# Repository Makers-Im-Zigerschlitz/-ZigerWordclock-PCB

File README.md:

# ZigerWordclock-PCB
KiCad PCB data for our OpenSource Wordclock

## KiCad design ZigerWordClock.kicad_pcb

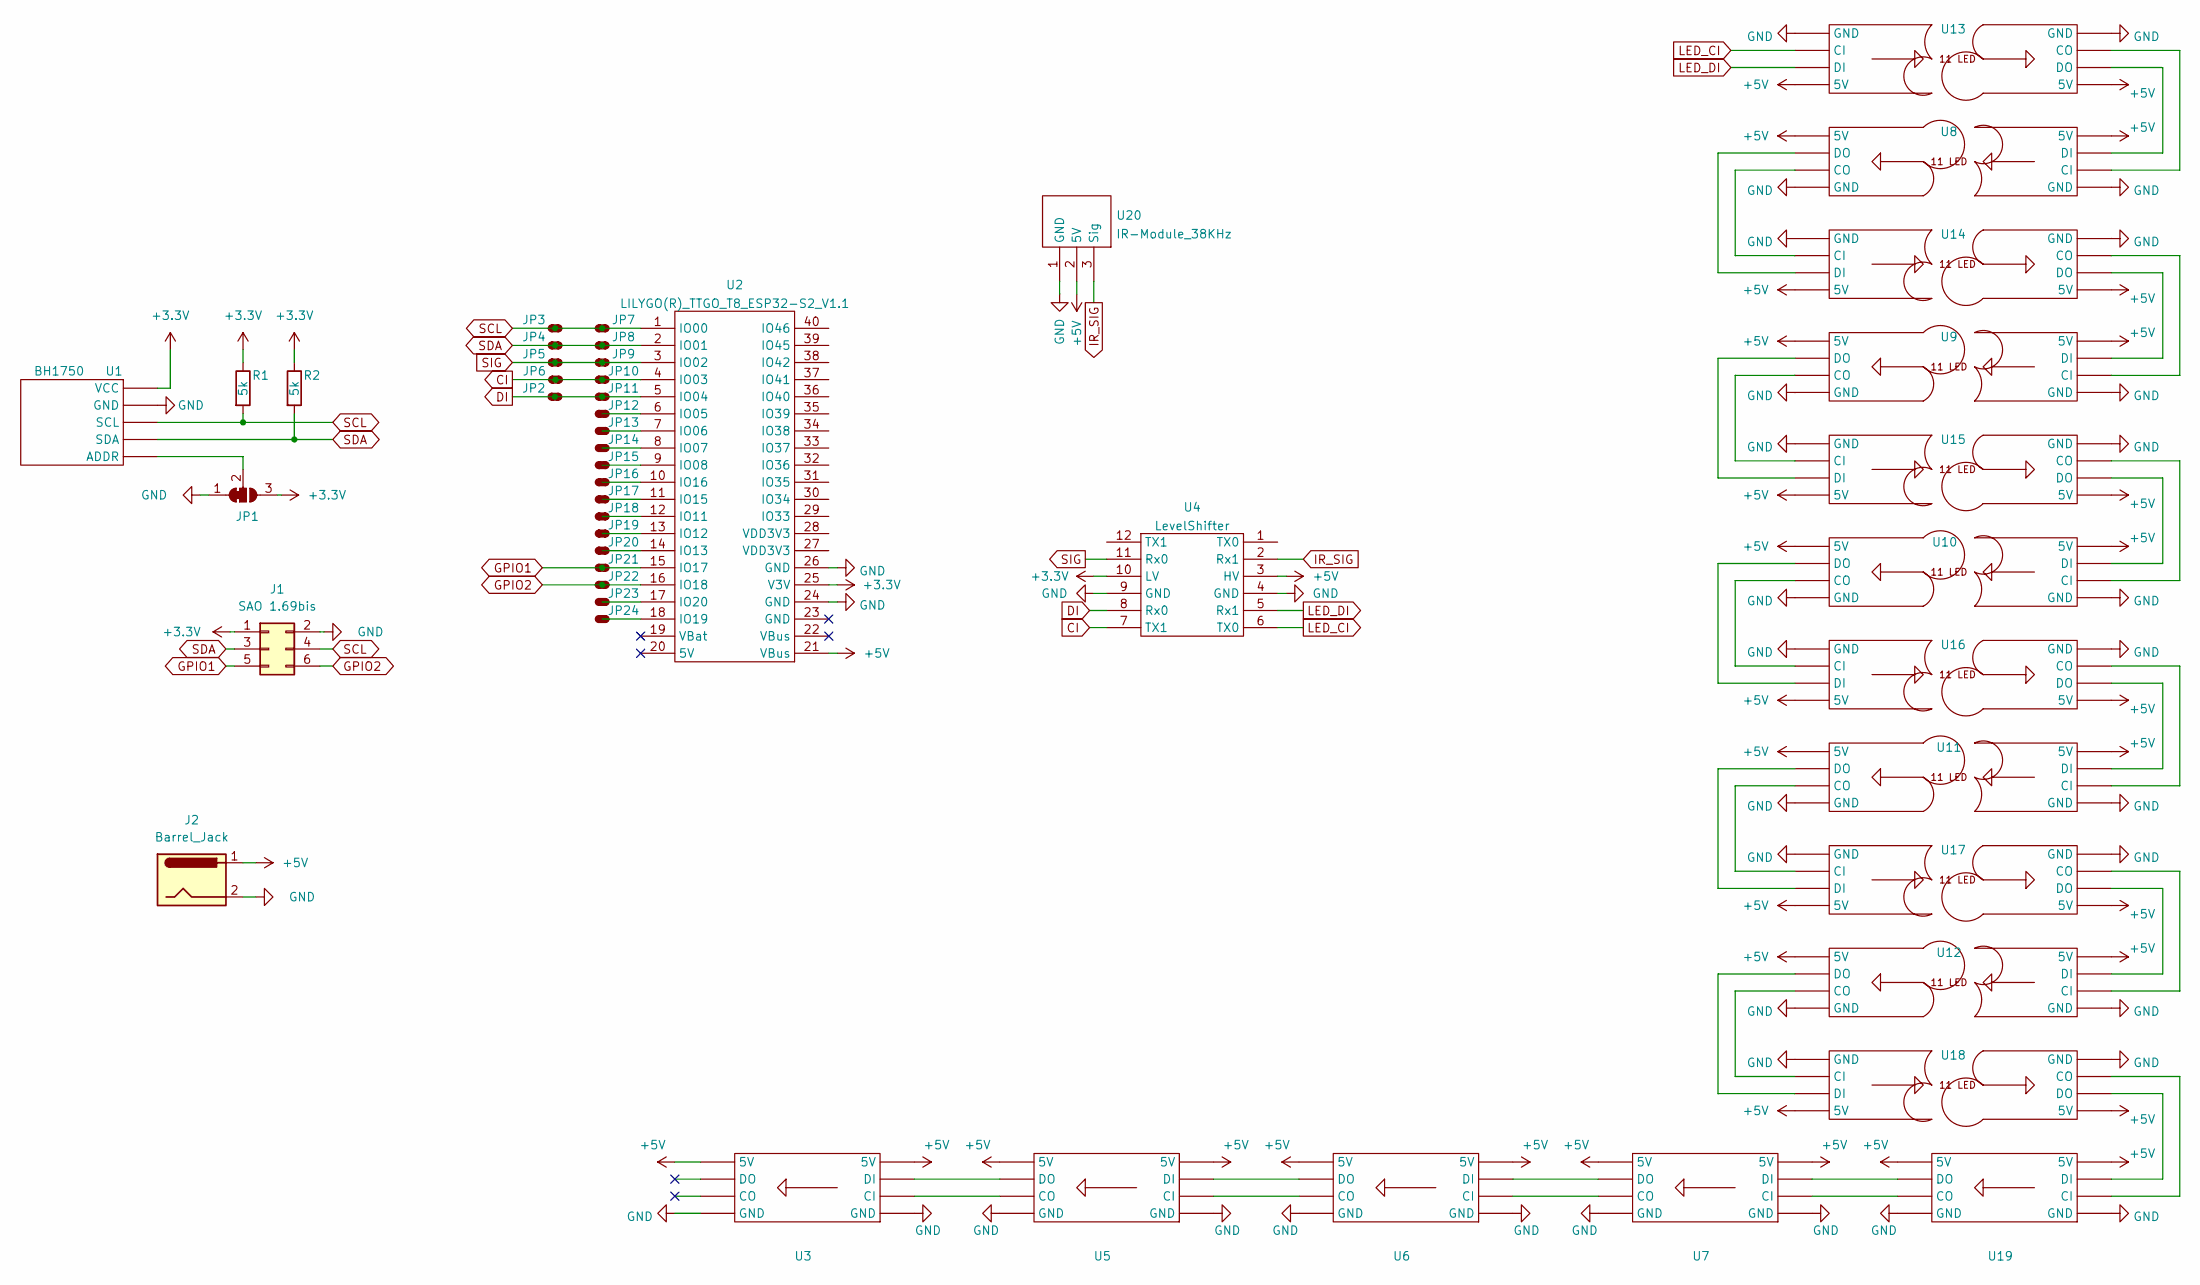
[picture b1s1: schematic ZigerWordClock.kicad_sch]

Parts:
J1: SAO 1.69bis; PinSocket_2x03_P2.54mm_Vertical_SMD
J2: Barrel_Jack; PinHeader_1x02_P2.54mm_Vertical
JP1: SolderJumper_3_Bridged12; SolderJumper-3_P1.3mm_Bridged12_RoundedPad1.0x1.5mm_NumberL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
JP2, JP3, JP4, JP5, JP6, JP7, JP8, JP9, JP10, JP11, JP12, JP13, JP14, JP15, JP16, JP17, JP18, JP19, JP20, JP21, JP22, JP23, JP24: Pad
R1, R2: 5k; R_Axial_DIN0207_L6.3mm_D2.5mm_P10.16mm_Horizontal
U1: BH1750; BH1750 Breakout Board
U2: LILYGO(R)_TTGO_T8_ESP32-S2_V1.1; LILYGO® TTGO T8 ESP32-S2 V1.1
U3, U5, U6, U7, U19: BTF-5V-060L-B_SK9822_LED_Strip_-_1_LED; BTF-5V-060L-B SK9822 LED Strip - 1 Segment
U4: LevelShifter
U8, U9, U10, U11, U12, U13, U14, U15, U16, U17, U18: BTF-5V-060L-B_SK9822_LED_Strip_-_11_LED; BTF-5V-060L-B SK9822 LED Strip - 11 Segment
U20: IR-Module_38KHz

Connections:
+3V3: J1.1, JP1.3 (B), R1.1, R2.1, U1.VCC, U2.25 (V3V), U4.10 (LV)
+5V: J2.1, U2.21 (VBus), U3.5V_1 (5V), U3.5V_2 (5V), U4.3 (HV), U5.5V_1 (5V), U5.5V_2 (5V), U6.5V_1 (5V), U6.5V_2 (5V), U7.5V_1 (5V), U7.5V_2 (5V), U8.5V_1 (5V), U8.5V_2 (5V), U9.5V_1 (5V), U9.5V_2 (5V), U10.5V_1 (5V), U10.5V_2 (5V), U11.5V_1 (5V), U11.5V_2 (5V), U12.5V_1 (5V), U12.5V_2 (5V), U13.5V_1 (5V), U13.5V_2 (5V), U14.5V_1 (5V), U14.5V_2 (5V), U15.5V_1 (5V), U15.5V_2 (5V), U16.5V_1 (5V), U16.5V_2 (5V), U17.5V_1 (5V), U17.5V_2 (5V), U18.5V_1 (5V), U18.5V_2 (5V), U19.5V_1 (5V), U19.5V_2 (5V), U20.2 (5V)
CI: JP6.1, JP10.1, U2.4 (IO03), U4.7 (TX1)
DI: JP2.1, JP11.1, U2.5 (IO04), U4.8 (Rx0)
GND: J1.2, J2.2, JP1.1 (A), U1.GND, U2.24 (GND), U2.26 (GND), U3.GND_1 (GND), U3.GND_2 (GND), U4.4 (GND), U4.9 (GND), U5.GND_1 (GND), U5.GND_2 (GND), U6.GND_1 (GND), U6.GND_2 (GND), U7.GND_1 (GND), U7.GND_2 (GND), U8.GND_1 (GND), U8.GND_2 (GND), U9.GND_1 (GND), U9.GND_2 (GND), U10.GND_1 (GND), U10.GND_2 (GND), U11.GND_1 (GND), U11.GND_2 (GND), U12.GND_1 (GND), U12.GND_2 (GND), U13.GND_1 (GND), U13.GND_2 (GND), U14.GND_1 (GND), U14.GND_2 (GND), U15.GND_1 (GND), U15.GND_2 (GND), U16.GND_1 (GND), U16.GND_2 (GND), U17.GND_1 (GND), U17.GND_2 (GND), U18.GND_1 (GND), U18.GND_2 (GND), U19.GND_1 (GND), U19.GND_2 (GND), U20.1 (GND)
GPIO1: J1.5, JP21.1, U2.15 (IO17)
GPIO2: J1.6, JP22.1, U2.16 (IO18)
IR_SIG: U4.2 (Rx1), U20.3 (Sig)
LED_CI: U4.6 (TX0), U13.CI
LED_DI: U4.5 (Rx1), U13.DI
unnamed: JP1.2 (C), U1.ADDR
unnamed: JP12.1, U2.6 (IO05)
unnamed: JP13.1, U2.7 (IO06)
unnamed: JP14.1, U2.8 (IO07)
unnamed: JP15.1, U2.9 (IO08)
unnamed: JP16.1, U2.10 (IO16)
unnamed: JP17.1, U2.11 (IO15)
unnamed: JP18.1, U2.12 (IO11)
unnamed: JP19.1, U2.13 (IO12)
unnamed: JP20.1, U2.14 (IO13)
unnamed: JP23.1, U2.17 (IO20)
unnamed: JP24.1, U2.18 (IO19)
unnamed: U3.CI, U5.CO
unnamed: U3.DI, U5.DO
unnamed: U5.CI, U6.CO
unnamed: U5.DI, U6.DO
unnamed: U6.CI, U7.CO
unnamed: U6.DI, U7.DO
unnamed: U10.CI, U15.CO
unnamed: U10.CO, U16.CI
unnamed: U10.DI, U15.DO
unnamed: U10.DO, U16.DI
unnamed: U11.CI, U16.CO
unnamed: U11.CO, U17.CI
unnamed: U11.DI, U16.DO
unnamed: U11.DO, U17.DI
unnamed: U12.CI, U17.CO
unnamed: U12.CO, U18.CI
unnamed: U12.DI, U17.DO
unnamed: U12.DO, U18.DI
unnamed: U8.CI, U13.CO
unnamed: U8.DI, U13.DO
unnamed: U8.CO, U14.CI
unnamed: U9.CI, U14.CO
unnamed: U8.DO, U14.DI
unnamed: U9.DI, U14.DO
unnamed: U9.CO, U15.CI
unnamed: U9.DO, U15.DI
unnamed: U18.CO, U19.CI
unnamed: U18.DO, U19.DI
unnamed: U7.CI, U19.CO
unnamed: U7.DI, U19.DO
SCL: J1.4, JP3.1, JP7.1, R1.2, U1.SCL, U2.1 (IO00)
SDA: J1.3, JP4.1, JP8.1, R2.2, U1.SDA, U2.2 (IO01)
SIG: JP5.1, JP9.1, U2.3 (IO02), U4.11 (Rx0)

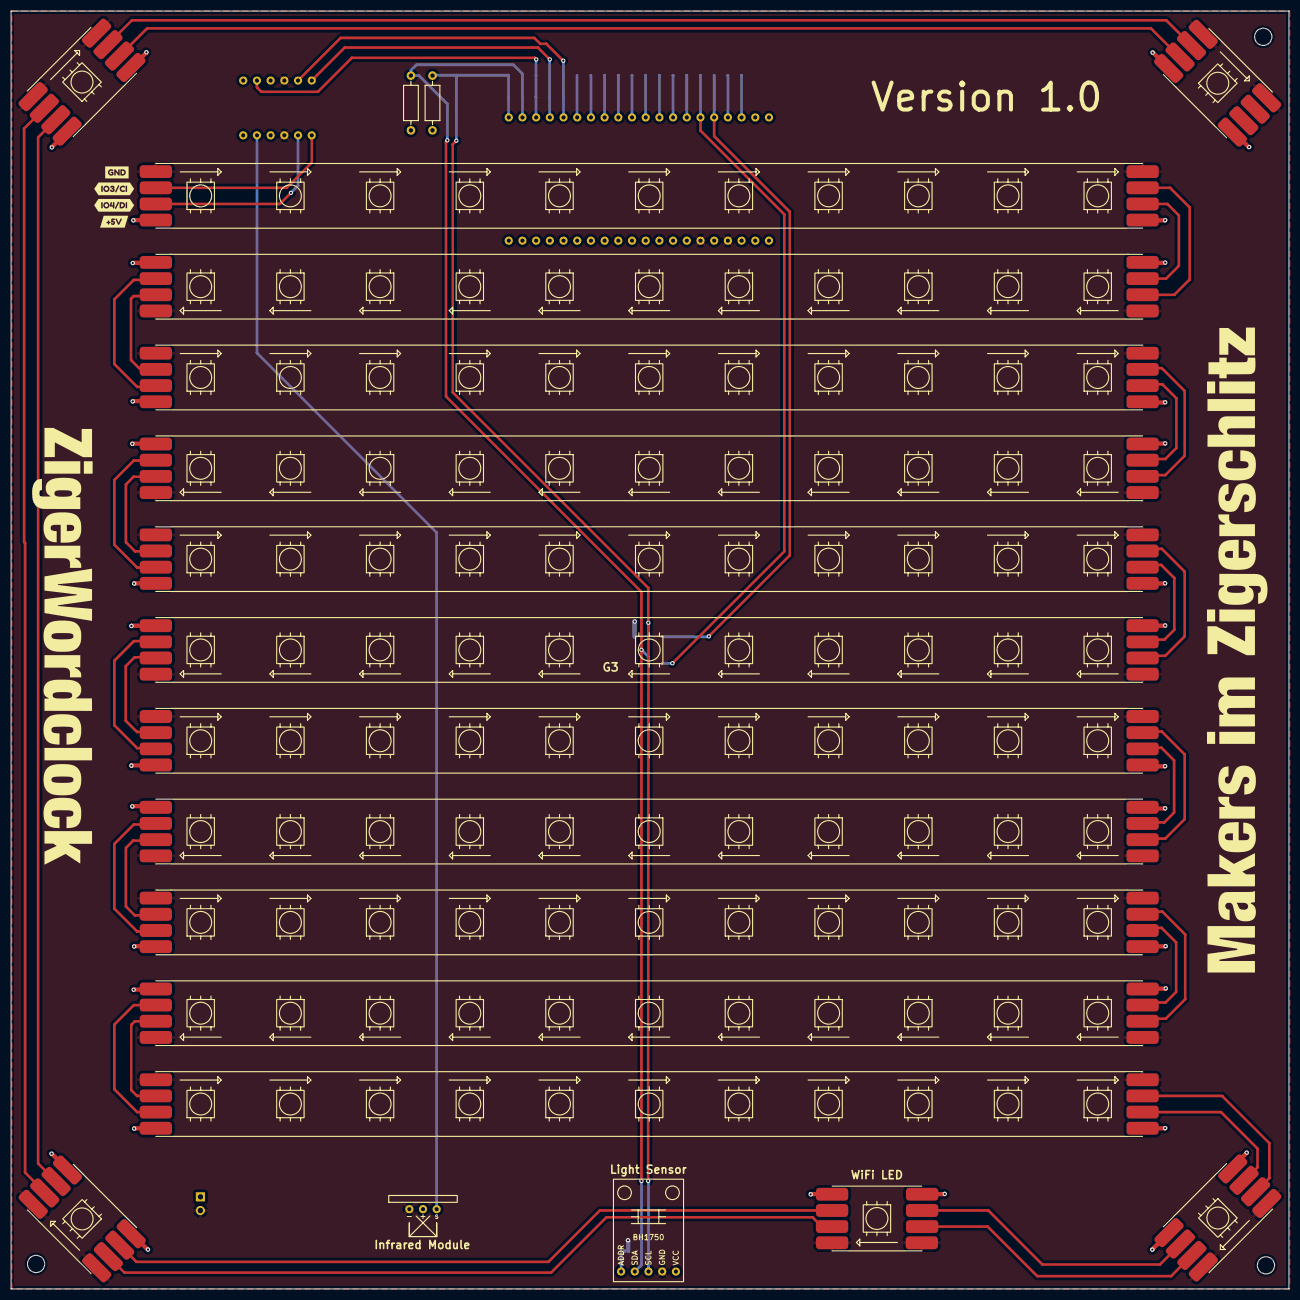
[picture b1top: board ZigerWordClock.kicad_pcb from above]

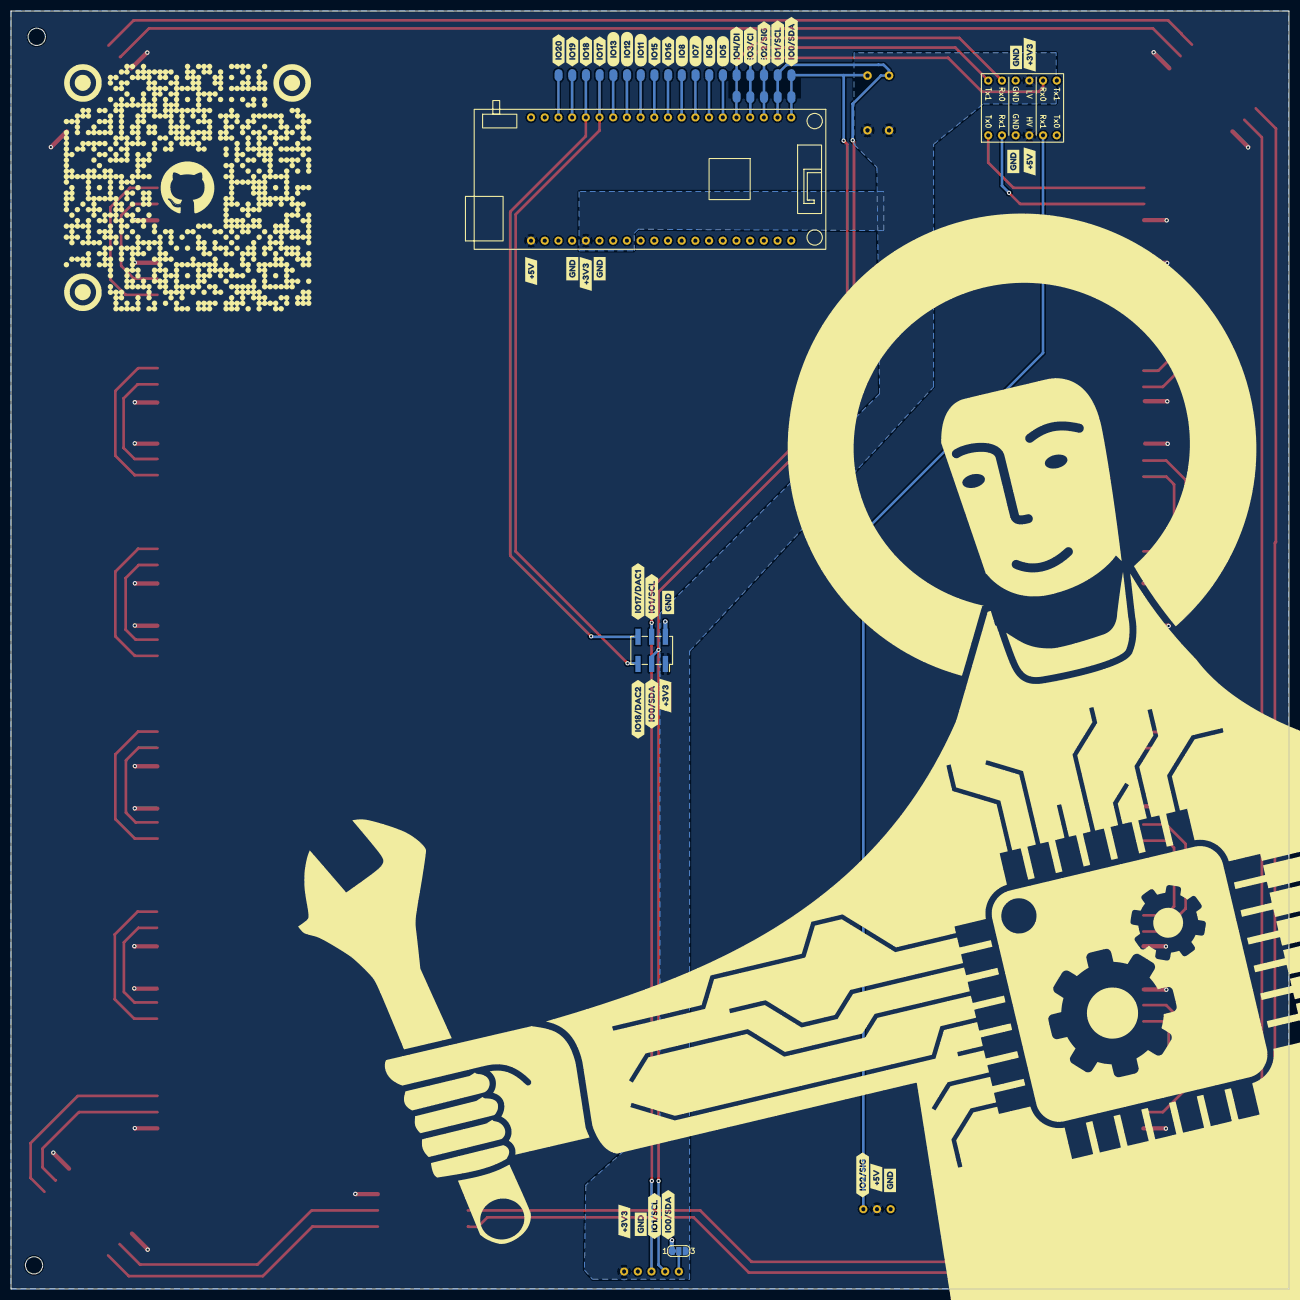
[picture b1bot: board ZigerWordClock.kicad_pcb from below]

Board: 2 copper layers, 237.0 x 237.0 mm, 94 parts (68 on the bottom side), 55 nets.

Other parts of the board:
G1: LOGO; Schriftzug MiZ
G2: LOGO; Schriftzug Wordclock
G3: LOGO; BackLogo
kibuzzard-620DE80D, kibuzzard-620DE80D#2, kibuzzard-620DE80D#3: G***; kibuzzard-620DE80D
kibuzzard-620DEA12, kibuzzard-620DEA12#2, kibuzzard-620DEA12#3: G***; kibuzzard-620DEA12
kibuzzard-620DEA49, kibuzzard-620DEA49#2: G***; kibuzzard-620DEA49
kibuzzard-620DEA86, kibuzzard-620DEA86#2: G***; kibuzzard-620DEA86
kibuzzard-620DEAF9: G***; kibuzzard-620DEAF9
kibuzzard-620DEB10: G***; kibuzzard-620DEB10
kibuzzard-620DEB75: G***; kibuzzard-620DEB75
kibuzzard-620DEB83: G***; kibuzzard-620DEB83
kibuzzard-620DEBCF, kibuzzard-620DEBCF#2: G***; kibuzzard-620DEBCF
kibuzzard-620DEC17: G***; kibuzzard-620DEC17
kibuzzard-620DEC24: G***; kibuzzard-620DEC24
kibuzzard-620DECE9: G***; kibuzzard-620DECE9
kibuzzard-620DED0B: G***; kibuzzard-620DED0B
kibuzzard-620DED4F: G***; kibuzzard-620DED4F
kibuzzard-620DED15: G***; kibuzzard-620DED15
kibuzzard-620DED33: G***; kibuzzard-620DED33
kibuzzard-620DED42: G***; kibuzzard-620DED42
kibuzzard-620DED59: G***; kibuzzard-620DED59
kibuzzard-620DEDB9: G***; kibuzzard-620DEDB9
kibuzzard-620DEDD7: G***; kibuzzard-620DEDD7
kibuzzard-620DEFD1, kibuzzard-620DEFD1#2, kibuzzard-620DEFD1#3, kibuzzard-620DEFD1#4: G***; kibuzzard-620DEFD1
kibuzzard-620DF0B9, kibuzzard-620DF0B9#2, kibuzzard-620DF0B9#3, kibuzzard-620DF0B9#4, kibuzzard-620DF0B9#5, kibuzzard-620DF0B9#6, kibuzzard-620DF0B9#7, kibuzzard-620DF0B9#8: G***; kibuzzard-620DF0B9
kibuzzard-620DF03F, kibuzzard-620DF03F#2, kibuzzard-620DF03F#3, kibuzzard-620DF03F#4: G***; kibuzzard-620DF03F

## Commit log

2022-02-14 LEDs added
2022-02-14 Add STEP Files für LEDs
2022-02-14 Added BH1750 3D model to footprint
2022-02-14 Added LevelShifter
2022-02-14 LevelShifter Step File added and importet to footprint
2022-02-14 Pins fixed in library
2022-02-14 Fixed library and missing footprints for i2c resistors
2022-02-14 Adds ir receiver to schematic and board
2022-02-15 Added some connections
2022-02-16 finalized pins, fixed ESP libs
2022-02-16 pads added to libs
2022-02-16 first routing done
2022-02-17 Pin labels added
2022-02-20 Added STEP-file
2022-02-20 Changed .wrl to .step in footprints
    With this full .step board exports include all the subcomponents
2022-02-20 Added silkscreen graphics and version number
2022-02-20 Add mounting holes, moved barrel jack, adjusted graphics
2022-02-22 Added JLCPCB DRC Rules
2022-02-22 Moved copper traces and created GERBER Files
2022-02-22 Extends .gitignore for backups
2022-02-22 compabiliy with the display ESP32 module
2022-02-22 compatibilty with display version
2022-02-23 backup cleanup
2022-02-23 gerber added
2022-02-23 ready for production
2022-02-23 repo cleanup
2022-02-26 mounting holes fixed @
2022-02-26 mounting holes fixed
2022-02-26 Mouning holes fixed
